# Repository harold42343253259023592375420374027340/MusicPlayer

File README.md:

# WARNING
So this is a music player i tossed together in about 10hrs most likely does not work, im gonna build it and notify if it does.

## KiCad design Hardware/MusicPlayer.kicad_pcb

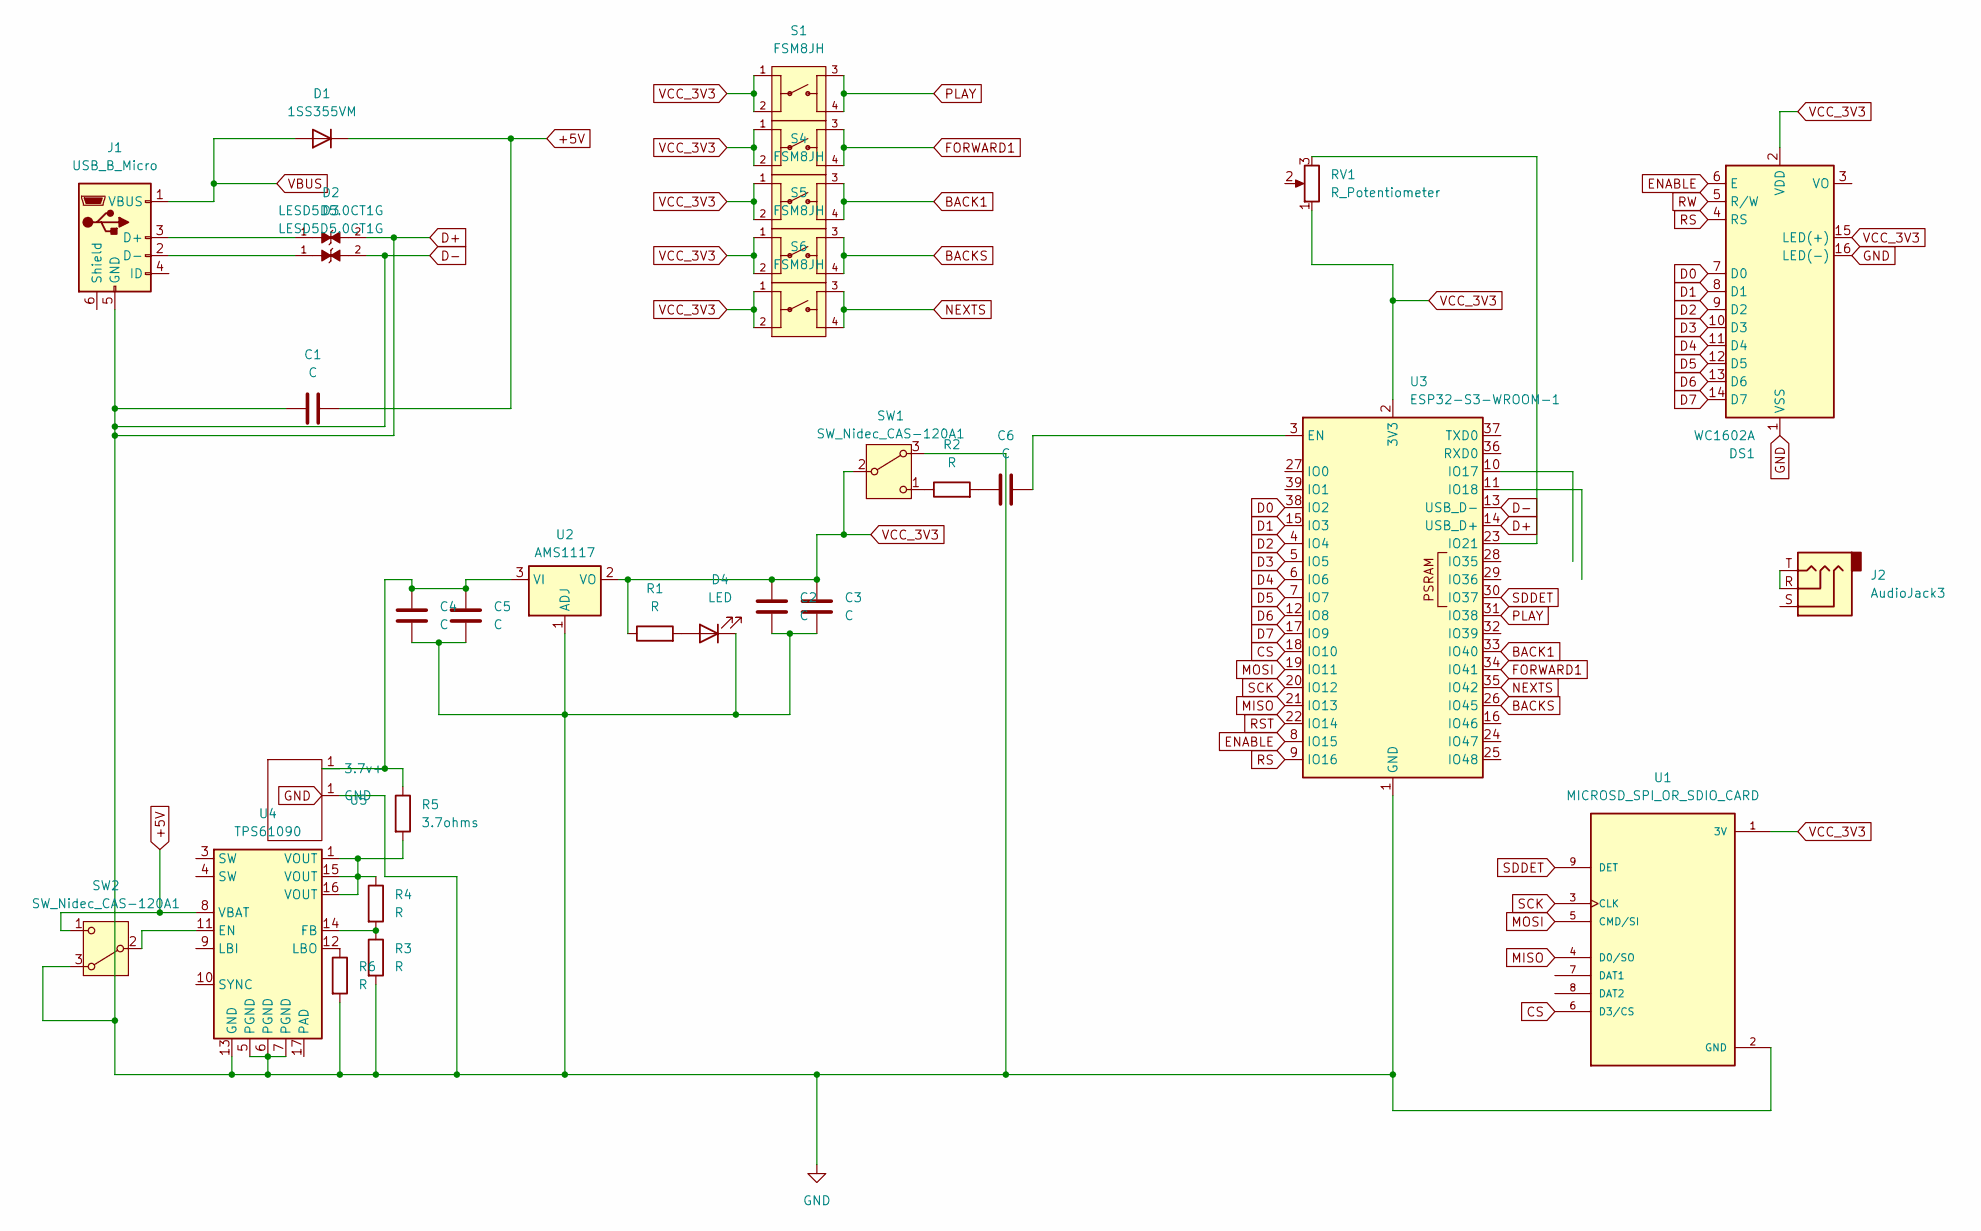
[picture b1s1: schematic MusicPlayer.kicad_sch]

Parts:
C1, C2, C3, C4, C5, C6: C; C_0201_0603Metric
D1: 1SS355VM; D_SOD-323F
D2, D3: LESD5D5.0CT1G; TVS_LESD5D5.0CT1G; PARTREV O
D4: LED; LED_0201_0603Metric
DS1: WC1602A
J1: USB_B_Micro; USB_Micro-B_Amphenol_10103594-0001LF_Horizontal
J2: AudioJack3; Jack_3.5mm_CUI_SJ-3523-SMT_Horizontal
R1, R2, R3, R4, R6: R; R_0201_0603Metric
R5: 3.7ohms; R_0201_0603Metric
RV1: R_Potentiometer; Potentiometer_Bourns_3314S_Horizontal
S1, S3, S4, S5, S6: FSM8JH; SW_FSM8JH; PARTREV C10
SW1, SW2: SW_Nidec_CAS-120A1; Nidec_Copal_CAS-120A
U1: MICROSD_SPI_OR_SDIO_CARD; MODULE_MICROSD_SPI_OR_SDIO_CARD; PARTREV B
U2: AMS1117; SOT-223-3_TabPin2
U3: ESP32-S3-WROOM-1; ESP32-S3-WROOM-1U
U4: TPS61090; Texas_RSA_VQFN-16-1EP_4x4mm_P0.65mm_EP2.7x2.7mm_ThermalVias
U5: Untitled

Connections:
+5V: C1.2, D1.1 (K), SW2.1 (C), U4.8 (VBAT)
BACK1: S4.3, S4.4, U3.33 (IO40)
BACKS: S5.3, S5.4, U3.26 (IO45)
CS: U1.6 (D3/CS), U3.18 (IO10)
D0: DS1.7 (D0), U3.38 (IO2)
D1: DS1.8 (D1), U3.15 (IO3)
D2: DS1.9 (D2), U3.4 (IO4)
D3: DS1.10 (D3), U3.5 (IO5)
D4: DS1.11 (D4), U3.6 (IO6)
D5: DS1.12 (D5), U3.7 (IO7)
D6: DS1.13 (D6), U3.12 (IO8)
D7: DS1.14 (D7), U3.17 (IO9)
D+: C1.1, C2.2, C3.2, C4.2, C5.2, D2.2, D3.2, D4.1 (K), DS1.1 (VSS), DS1.16 (LED(-)), J1.5 (GND), R3.2, R6.2, SW1.3 (A), SW2.3 (A), U1.2 (GND), U2.1 (ADJ), U3.1 (GND), U3.13 (USB_D-), U3.14 (USB_D+), U3.40 (GND), U3.41 (GND), U4.5 (PGND), U4.6 (PGND), U4.7 (PGND), U4.13 (GND), U5.1
ENABLE: DS1.6 (E), U3.8 (IO15)
FORWARD1: S3.3, S3.4, U3.34 (IO41)
MISO: U1.4 (D0/SO), U3.21 (IO13)
MOSI: U1.5 (CMD/SI), U3.19 (IO11)
NEXTS: S6.3, S6.4, U3.35 (IO42)
unnamed: C6.1, R2.2
unnamed: D4.2 (A), R1.2
unnamed: D2.1, J1.3 (D+)
unnamed: D3.1, J1.2 (D-)
unnamed: J2.R, J2.T
unnamed: R4.1, R5.2, U4.1 (VOUT), U4.15 (VOUT), U4.16 (VOUT)
unnamed: R2.1, SW1.1 (C)
unnamed: SW2.2 (B), U4.11 (EN)
unnamed: C4.1, C5.1, R5.1, U2.3 (VI), U5.1
unnamed: C6.2, U3.3 (EN)
unnamed: RV1.3, U3.23 (IO21)
unnamed: R3.1, R4.2, U4.14 (FB)
unnamed: R6.1, U4.12 (LBO)
PLAY: S1.3, S1.4, U3.31 (IO38)
RS: DS1.4 (RS), U3.9 (IO16)
RST: U3.22 (IO14)
RW: DS1.5 (R/W)
SCK: U1.3 (CLK), U3.20 (IO12)
SDDET: U1.9 (DET), U3.30 (IO37)
VBUS: D1.2 (A), J1.1 (VBUS)
VCC_3V3: C2.1, C3.1, DS1.2 (VDD), DS1.15 (LED(+)), R1.1, RV1.1, S1.1, S1.2, S3.1, S3.2, S4.1, S4.2, S5.1, S5.2, S6.1, S6.2, SW1.2 (B), U1.1 (3V), U2.2 (VO), U3.2 (3V3)

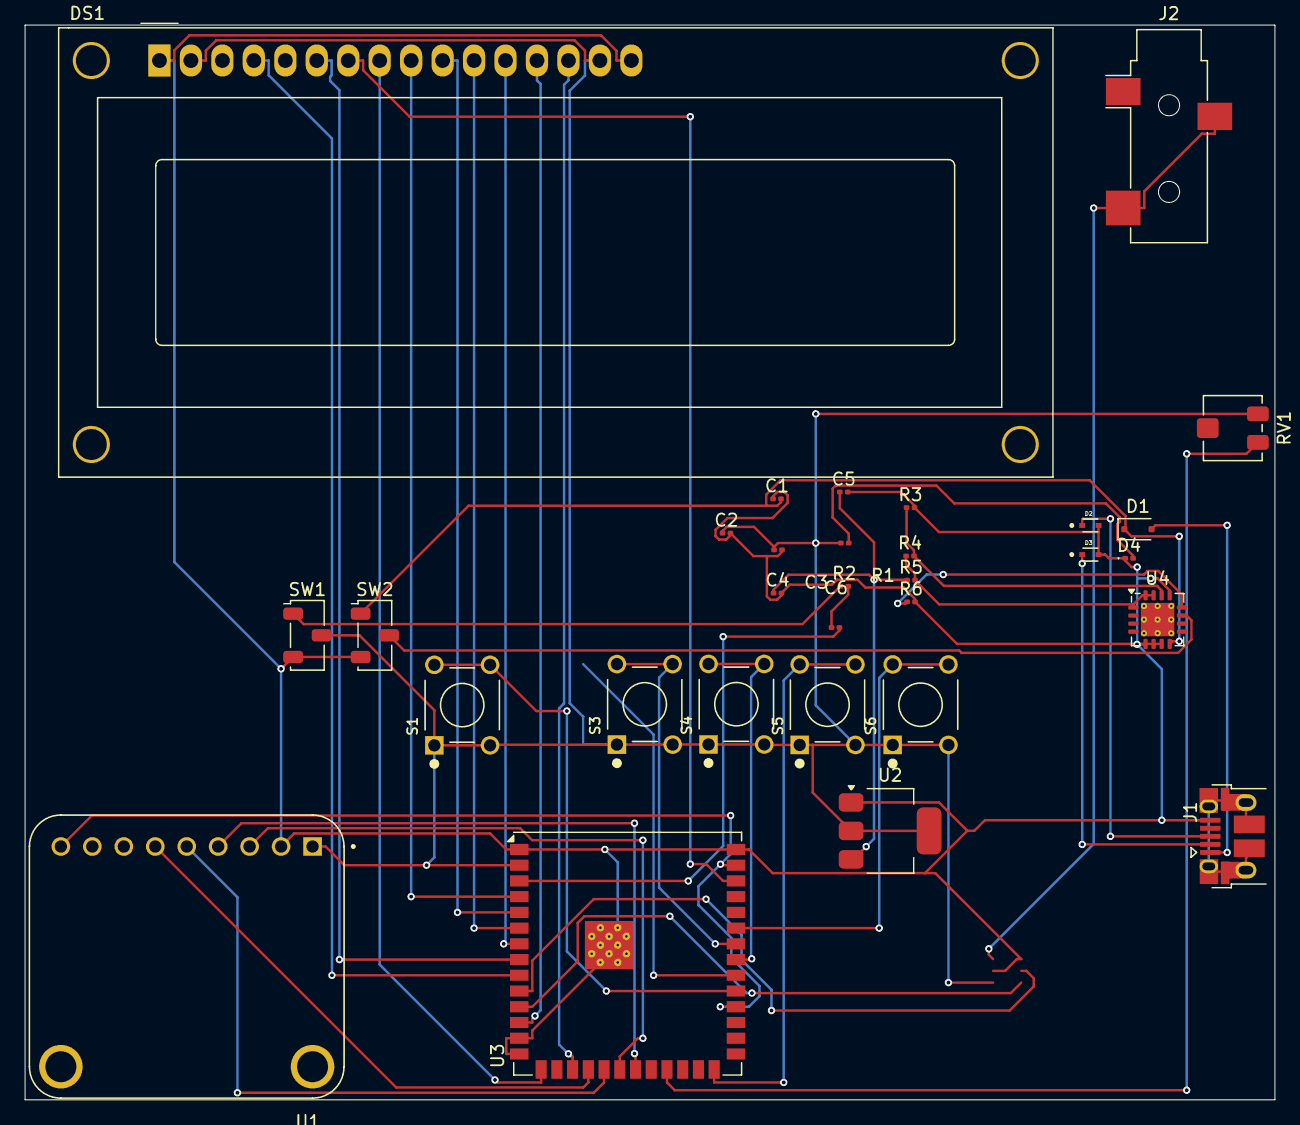
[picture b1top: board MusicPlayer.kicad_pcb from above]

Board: 2 copper layers, 100.9 x 86.8 mm, 32 parts (1 on the bottom side), 37 nets.

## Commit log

2025-07-03 init repository
2025-07-03 Create LICENSE
2025-07-04 added the button control + volume control
2025-07-04 bux fixed and updated the schematic with a DAC for sound output
2025-07-07 temporarily removed DAC, i think i will change the MCU to one with a built in DAC
2025-07-07 fixed spelling and fixing the logic for playing music
